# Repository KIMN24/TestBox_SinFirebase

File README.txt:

Esta es la ultima version de codigo que se tiene de la test box 2026.

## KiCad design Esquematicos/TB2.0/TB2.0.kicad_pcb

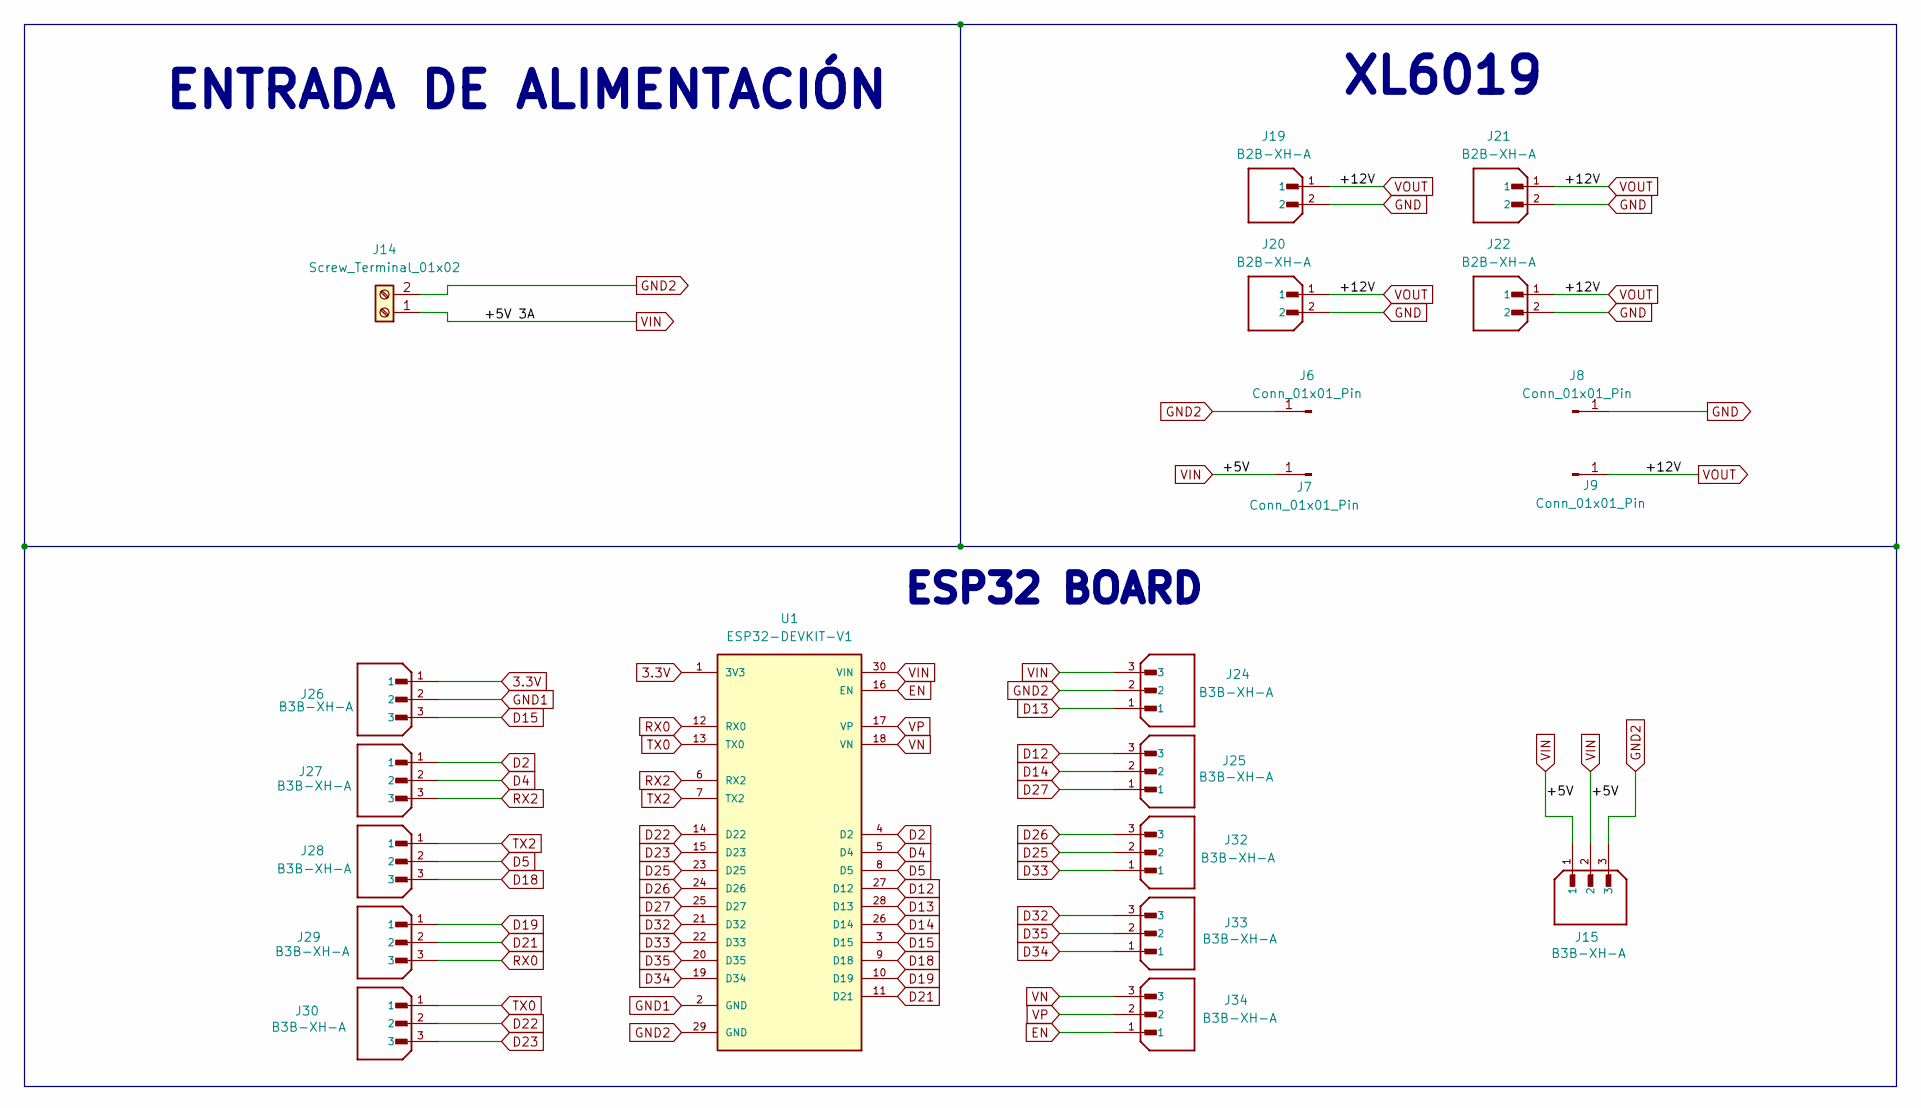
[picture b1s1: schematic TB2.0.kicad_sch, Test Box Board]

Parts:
J6, J7, J8, J9: Conn_01x01_Pin; PinHeader_1x01_P2.54mm_Vertical
J14: Screw_Terminal_01x02; TerminalBlock_MaiXu_MX126-5.0-02P_1x02_P5.00mm
J15, J24, J25, J26, J27, J28, J29, J30, J32, J33, J34: B3B-XH-A; JST_B3B-XH-A; PARTREV 7/4/21
J19, J20, J21, J22: B2B-XH-A; JST_B2B-XH-A; PARTREV N/A
U1: ESP32-DEVKIT-V1; MODULE_ESP32_DEVKIT_V1; PARTREV N/A

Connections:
3.3V: J26.1, U1.1 (3V3)
D2: J27.1, U1.4 (D2)
D4: J27.2, U1.5 (D4)
D5: J28.2, U1.8 (D5)
D12: J25.3, U1.27 (D12)
D13: J24.1, U1.28 (D13)
D14: J25.2, U1.26 (D14)
D15: J26.3, U1.3 (D15)
D18: J28.3, U1.9 (D18)
D19: J29.1, U1.10 (D19)
D21: J29.2, U1.11 (D21)
D22: J30.2, U1.14 (D22)
D23: J30.3, U1.15 (D23)
D25: J32.2, U1.23 (D25)
D26: J32.3, U1.24 (D26)
D27: J25.1, U1.25 (D27)
D32: J33.3, U1.21 (D32)
D33: J32.1, U1.22 (D33)
D34: J33.1, U1.19 (D34)
D35: J33.2, U1.20 (D35)
EN: J34.1, U1.16 (EN)
GND: J8.1, J19.2, J20.2, J21.2, J22.2
GND1: J26.2, U1.2 (GND)
GND2: J6.1, J14.2, J15.3, J24.2, U1.29 (GND)
RX0: J29.3, U1.12 (RX0)
RX2: J27.3, U1.6 (RX2)
TX0: J30.1, U1.13 (TX0)
TX2: J28.1, U1.7 (TX2)
VIN: J7.1, J14.1, J15.1, J15.2, J24.3, U1.30 (VIN)
VN: J34.3, U1.18 (VN)
VOUT: J9.1, J19.1, J20.1, J21.1, J22.1
VP: J34.2, U1.17 (VP)

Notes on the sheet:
XL6019
ESP32 BOARD
ENTRADA DE ALIMENTACIÓN

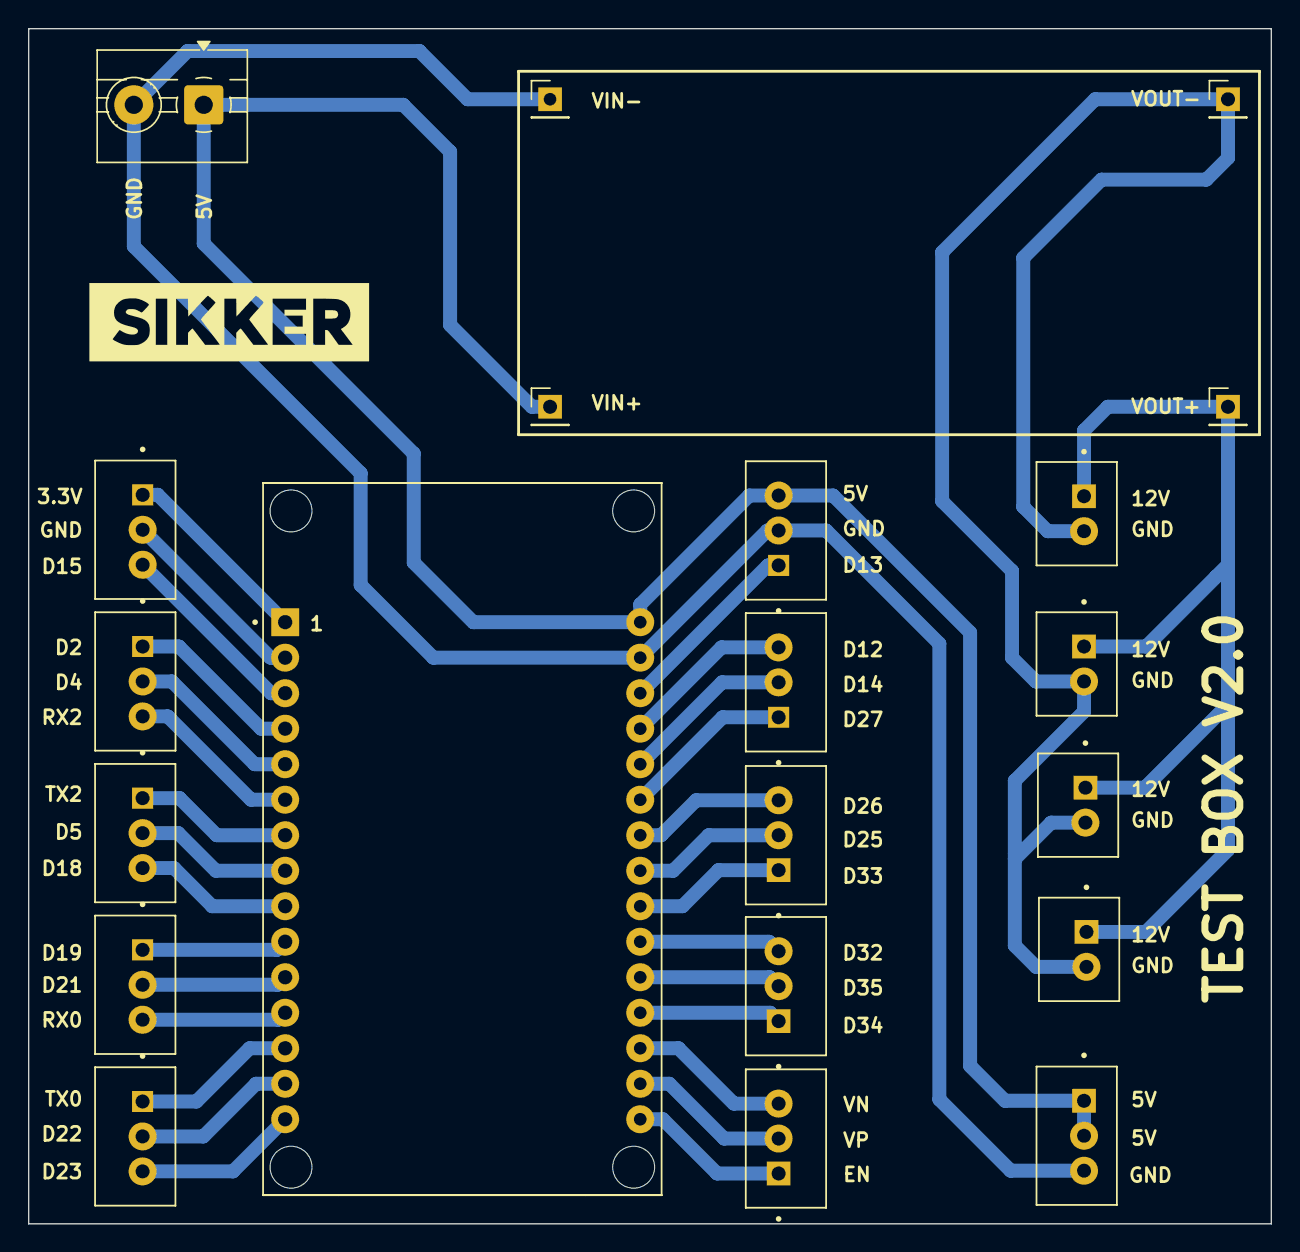
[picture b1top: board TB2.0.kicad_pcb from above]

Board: 2 copper layers, 88.9 x 85.5 mm, 21 parts (0 on the bottom side), 32 nets.

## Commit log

2025-10-31 Primera versión Test Box
2025-12-16 Fix de eventos (L0-L2) y Fix de utils(Relays)
2025-12-16 Versión con conteos guardados localmente
2026-01-09 Versión 1.0 TestBox
2026-04-23 Se implemento FreeRtos 2026
2026-06-03 Nueva versi+on 2026
2026-06-29 Se agrego archivos CAD y esquematicos
2026-06-29 Update README with latest version information
